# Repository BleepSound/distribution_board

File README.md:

---
permalink: /index.html
layout: single
---

# Distribution board

Basic distribution board, with 12 IDC headers.

10 pins IDC headers used on this board (Because I don't use any 16 pin ones anyway).

## Schematics

## BoM

[See bom](documentation/bom/Distrib_V1.0--iBoM.html)

You can donwload the bom in excel format [here](https://github.com/BleepSound/distribution_board/releases/download/v1.0/Distrib_V1.0--BoM.xlsx).

## Build Informations

:warning: Use M3 standoff/screws to fasten it in place in your eurorack case.

## Images

## Download

Follow this link if you want to dowload the latest version of gerber files, schematic, kicad files...

:arrow_down: [**Download**](https://github.com/BleepSound/distribution_board/releases)

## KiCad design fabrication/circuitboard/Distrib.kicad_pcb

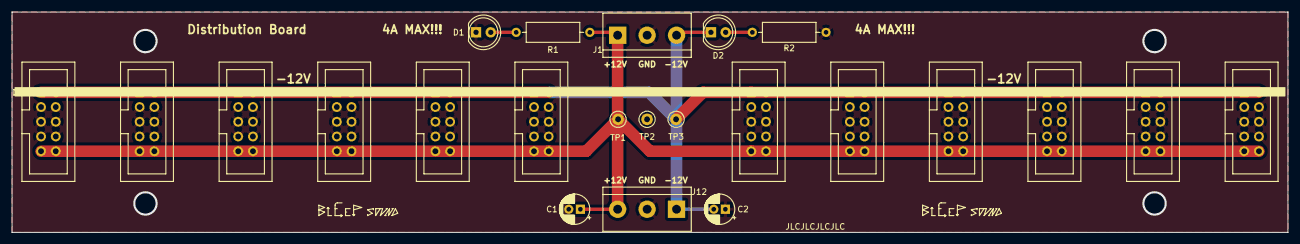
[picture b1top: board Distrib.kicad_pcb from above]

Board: 2 copper layers, 220.0 x 38.0 mm, 23 parts (0 on the bottom side), 5 nets.

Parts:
C1, C2: 100µF; CP_Radial_D5.0mm_P2.00mm
D1, D2: LED; LED_D5.0mm_Clear
J1: Power Input; TerminalBlock_bornier-3_P5.08mm
J2, J3, J4, J5, J6, J7, J8, J9, J10, J11, J13, J14: Power connector; IDC-Header_2x05_P2.54mm_Vertical
J12: Power Output; TerminalBlock_bornier-3_P5.08mm
R1, R2: 2.2k; R_Axial_DIN0309_L9.0mm_D3.2mm_P12.70mm_Horizontal
TP1: +V; TestPoint_Keystone_5000-5004_Miniature
TP2: GND; TestPoint_Keystone_5000-5004_Miniature
TP3: -V; TestPoint_Keystone_5000-5004_Miniature

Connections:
+12V: C1.1, J1.1, J2.9, J2.10, J3.9, J3.10, J4.9, J4.10, J5.9, J5.10, J6.9, J6.10, J7.9, J7.10, J8.9, J8.10, J9.9, J9.10, J10.9, J10.10, J11.9, J11.10, J12.3, J13.9, J13.10, J14.9, J14.10, R1.2, TP1.1
-12V: C2.2, D2.1 (K), J1.3, J2.1, J2.2, J3.1, J3.2, J4.1, J4.2, J5.1, J5.2, J6.1, J6.2, J7.1, J7.2, J8.1, J8.2, J9.1, J9.2, J10.1, J10.2, J11.1, J11.2, J12.1, J13.1, J13.2, J14.1, J14.2, TP3.1
GND: C1.2, C2.1, D1.1 (K), J1.2, J2.3, J2.4, J2.5, J2.6, J2.7, J2.8, J3.3, J3.4, J3.5, J3.6, J3.7, J3.8, J4.3, J4.4, J4.5, J4.6, J4.7, J4.8, J5.3, J5.4, J5.5, J5.6, J5.7, J5.8, J6.3, J6.4, J6.5, J6.6, J6.7, J6.8, J7.3, J7.4, J7.5, J7.6, J7.7, J7.8, J8.3, J8.4, J8.5, J8.6, J8.7, J8.8, J9.3, J9.4, J9.5, J9.6, J9.7, J9.8, J10.3, J10.4, J10.5, J10.6, J10.7, J10.8, J11.3, J11.4, J11.5, J11.6, J11.7, J11.8, J12.2, J13.3, J13.4, J13.5, J13.6, J13.7, J13.8, J14.3, J14.4, J14.5, J14.6, J14.7, J14.8, R2.1, TP2.1
unnamed: D1.2 (A), R1.1
unnamed: D2.2 (A), R2.2

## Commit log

2023-09-23 Add all Kicad files + Fab
2023-09-23 update readme links
2023-09-23 Fix schematic link
2024-10-20 setup github pages
